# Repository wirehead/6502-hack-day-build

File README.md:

# A 6502 Computer hack

## Step 0: Acquire parts

I'd purchased from Jameco a pair of 65C02's, a pair of 65C22's, a 6551, a MAX707 equivalent, plus some Am29F010 Flash RAM and some SRAM like ten years ago and it spent the years haunting me.

I'd intended to make my own Flash RAM burner but decided that was it's own project, so I decided to borrow the design for an EEPROM burner and decided that I might as well just get one of those reasonably cheap device burners off of Amazon instead.

I also picked up some fresh breadboards because I didn't want to evict my past project from it's board just yet.

## Step 1: Reset Circuit

*Start of hack day project*

Goal: There must be a circuit that will reset the CPU when the power comes up and de-bounce the reset button.

For whatever reason when I picked up the bits, MAX707's was a cheap microprocessor supervisor device that was available.  It'll send a reset pulse, it's got an input for a button that it'll debounce, it can send a brownout warning if you configure it right, and it's got both inverted and regular RESET rails.

I used a USB breakout adapter to drive the 5v rails.

## Step 2: Clock

Goal: There must be a 1 MHz clock.

I've got a half-can TTL oscillator.  Normally I manage to install them improperly because the dots are weird, so I had to look for the edge that's not rounded off and use that as a reference.

A lot of people start off with a crystal oscillator.  The problem with that is that you then wonder "Hey, did I do the oscillator right?" and goink with a capacitor somewhere in the 20 pF range and it sucks.  I went for a oscillator because those are dead-simple by comparison.

## Step 3: CPU going straight into a NOP generator

Goal: Get the CPU free-running on a NOP instruction

There's two ways to do this.  One way is really simple but ever-so-slightly unsafe, the other way is much safer.  You can either directly wire the binary pattern for a NOP instruction using wires to +5V and GND.  Or you can put resistors there, so that it won't fry if you get the bit pattern wrong and the CPU tries to write to the data bus.

I picked the second route, which means that D1, D3, D5, D6, and D7 all have a 4.7k ohm resistor to the +5V line and the three other lines (D0, D2, D4) are all tied to 47 ohm resistor on the GND line.

http://www.6502.org/mini-projects/nop-gen/nop-gen.htm

On Amazon, I got some ribbon cable that was already crimped to cute little one-pin housings.  I've divided these into little 8 bit bus lines and I'm routing them to where the Flash RAM is eventually going to live.

## Step 4: CPU + Flash RAM

Goal: Attach a device to the databus.

Okay, a few steps at once.

The goal is to have a relatively friendly modern build environment going.  I found one project that was actually showing how to use cc65 and makefiles as your build environment.  So that got me started on having a generated HEX file that I could burn to the ROM.

The Flash ROM has a slightly longer loop going.

The memory map here is pretty much:
 - 0x0000-0x7FFF - The first 32k of the flash ROM
 - 0x8000-0xFFFF - The first 32k of the flash ROM, mirrored

## Step 5: Attempt to connect CPU + Flash RAM + ACIA + Simple address decoder and experience voltage sag

Goal: Get to the point where my desktop computer will talk to the 6502

In the days of yore, you'd wire up an RS232 port to your computer.  This meant that you needed an extra chip to do the voltage conversion, generally a MAX232.  These days, pretty much everyone standardized on the FTDI connector, which is 2 signal lines, the RX and TX lines, and power and ground, in a 6 pin header that all of the popular USB serial port breakout boards connect to.

So I get my USB serial breakout adaptor connected, the Flash RAM and the ACIA.

The memory map here is pretty much:
 - 0x0000-0x7FFF - The ACIA, repeated every 4 bytes
 - 0x8000-0xFFFF - The first 32k of the flash ROM

It didn't work.

I had a few wires not correctly inserted into the right places, so I fixed that.

But the clock wasn't getting output from the Phi-1 and Phi-2 pins, and everything was stopped.

It took me a while.  I kept suspecting that the RESET line was the wrong one because it didn't seem to be triggering.  I figured out after a while that the power LED I'd helpfully added on the board felt dim, so I pulled the voltmeter out and realized that the voltage was around 3v, and the MAX707 triggers at 4.65V.

## Step 5.1: Voltage sag fix

I tried a few things.  It seemed to get a little bit better once I added duplicate power lines, but it was still floating around 4v - 4.2v.  I checked and I'm "only" using 80 mA of power.

I tried every USB adapter I had around to see if it was a crappy adaptor.

I'm not sure if it's a crappy breadboard or just all breadboards are like that.

I could have probably soldered up a point-to-point board, except I didn't have the sockets for all of the part sizes, nor did I have a sufficently large board... and that whole process is annoying.

*So, this is where the hack-day ended.*  But Hack Day is there till the end of the weekend, really.

Eventually, I asked on the adafruit discord and madbodger suggested and it was suggested to go to board-level regulation.  So I wired up a 12v power supply, so the power switch switches 12 volts, and then put a pair of 7805 regulators, one for each board.  And that got me to the point where I had happy 5v rails.

## Step 5.2: Single-step

I wired up a single-step clock by the end of the hack-day weekend.  This means that, instead of going at 1 MHz, I can clock one bit at a time.

Running the whole CPU + Flash RAM + ACIA stack: Inconclusive.

Running the whole CPU + Flash RAM + ACIA stack with the Flash in a tight loop: Why is the address line going in a weird direction?  Also, why are some of the lines silent with my logic probe?

I check and the silent line is within the spec for that particular part against the Rockwell datasheet.  Switch the logic probe to TTL mode and it starts to behave.  But it's going into places that it's not supposed to be going!

Switching back to the configuration from Step 3, but single-stepping:  Discover that the processor is very much not single-stepping properly anymore.  Seems like somewhere along the way I managed to zap it!

It also turns out that I only picked up one 65c02, which is a really poor life choice.

Second break: Waiting for a 65c02 to appear in the mail!

## Step 5.3: A giant step back where things start to work.

I ended up getting a few things.

First, I got a cheap $10 logic analyzer that was supported by Sigrok.  Second, I got a fresh set of chips from a different manufacturer, plus more ribbon cable so that it wouldn't risk devolving too far into a rat's nest.

Third, I decided that I'd solder up a tiny little board with the power circuit, the switch, the reset button, and the CPU clock.

I did a quick test and it looked like for a bit that the single-step clock might be a problem because it was looking a lot more like it was properly looping when I hooked up the logic analyzer.

I ended up stripping the board of most of the wiring and starting over with a fresh set of parts, starting off from having just a CPU and a NOP-generator, through the part where it runs a loop in Flash RAM.  I was able to use Sigrok to decode the values on the data bus and validate that it was doing the exact right thing.

Then I spent some time mucking around with serial lines, trying to make sure I had the right connections, and from there, I was finally able to get the serial port up.

Then I was able to go back and replace parts and determine that the 65c02 I had was somehow faulty.  Not sure if it was always bad and somehow a defective part made it into the supply chain or if I'd zapped it at some point in the past.

# Step 6: CPU + Flash RAM + ACIA + RAM

**Goal**: Make sure the board won't asplode when I plug it in.

I managed to not break the board after not working with it since last August.  I did a careful check, made sure the wires weren't plugged wrong, etc.  After doing a bunch of checks, I plug it in, connect to the serial port, and it says "▒▒▒▒▒ ▒▒▒▒▒!" instead of "Hello World!"

It turns out that one of the wires between the 6551 serial controller and the 6502 had come loose.  But, because it was so close to working, even though the firmware was setting that bit of a register, it was almost working.

**Goal**: Get RAM hooked up and IO decoded

The 6502 is really nearly useless without some RAM, maybe about 256 bytes for the zero page and 256 bytes for the stack page.  Otherwise, all you've got is three registers to work with.

Most of the modern designs tend towards a relatively friendly and easy memory mapper circuit.  We started out just using an inverter on A15 to select between the ACIA and the RAM, but now we've got two devices and they are very different sizes, so the usual approach is to put an 8-input NAND gate on A14 down to A8 to get a control line for the IO.

I was kinda following [Dirk Grappendorf's tutorial](https://www.grappendorf.net/projects/6502-home-computer/) but I got myself slightly confused at the [RAM part](https://www.grappendorf.net/projects/6502-home-computer/ram.html) of things.

What it turns out worked better for me was to just wire up the complete set of IO deciders right away to mimic the [SBC-2](http://sbc.rictor.org/sch2.html) design as well as [a later section of Dirk Grappendorf's tutorial](https://www.grappendorf.net/projects/6502-home-computer/via-ports-and-timers-blinking-led.html) before trying to hook up the RAM.

The memory map here is pretty much:
 - 0x0000-0x7EFF - The RAM
 	+ 0x0000-0x00FF - Zero Page
 	+ 0x0100-0x01FF - Stack page
 	+ 0x0200-0x7EFF - Available memory
 - 0x7F00-0x7FFF - IO, where the first few bytes are the ACIA
 - 0x8000-0xFFFF - The first 32k of the flash ROM

The whole works is getting way too unreliable.

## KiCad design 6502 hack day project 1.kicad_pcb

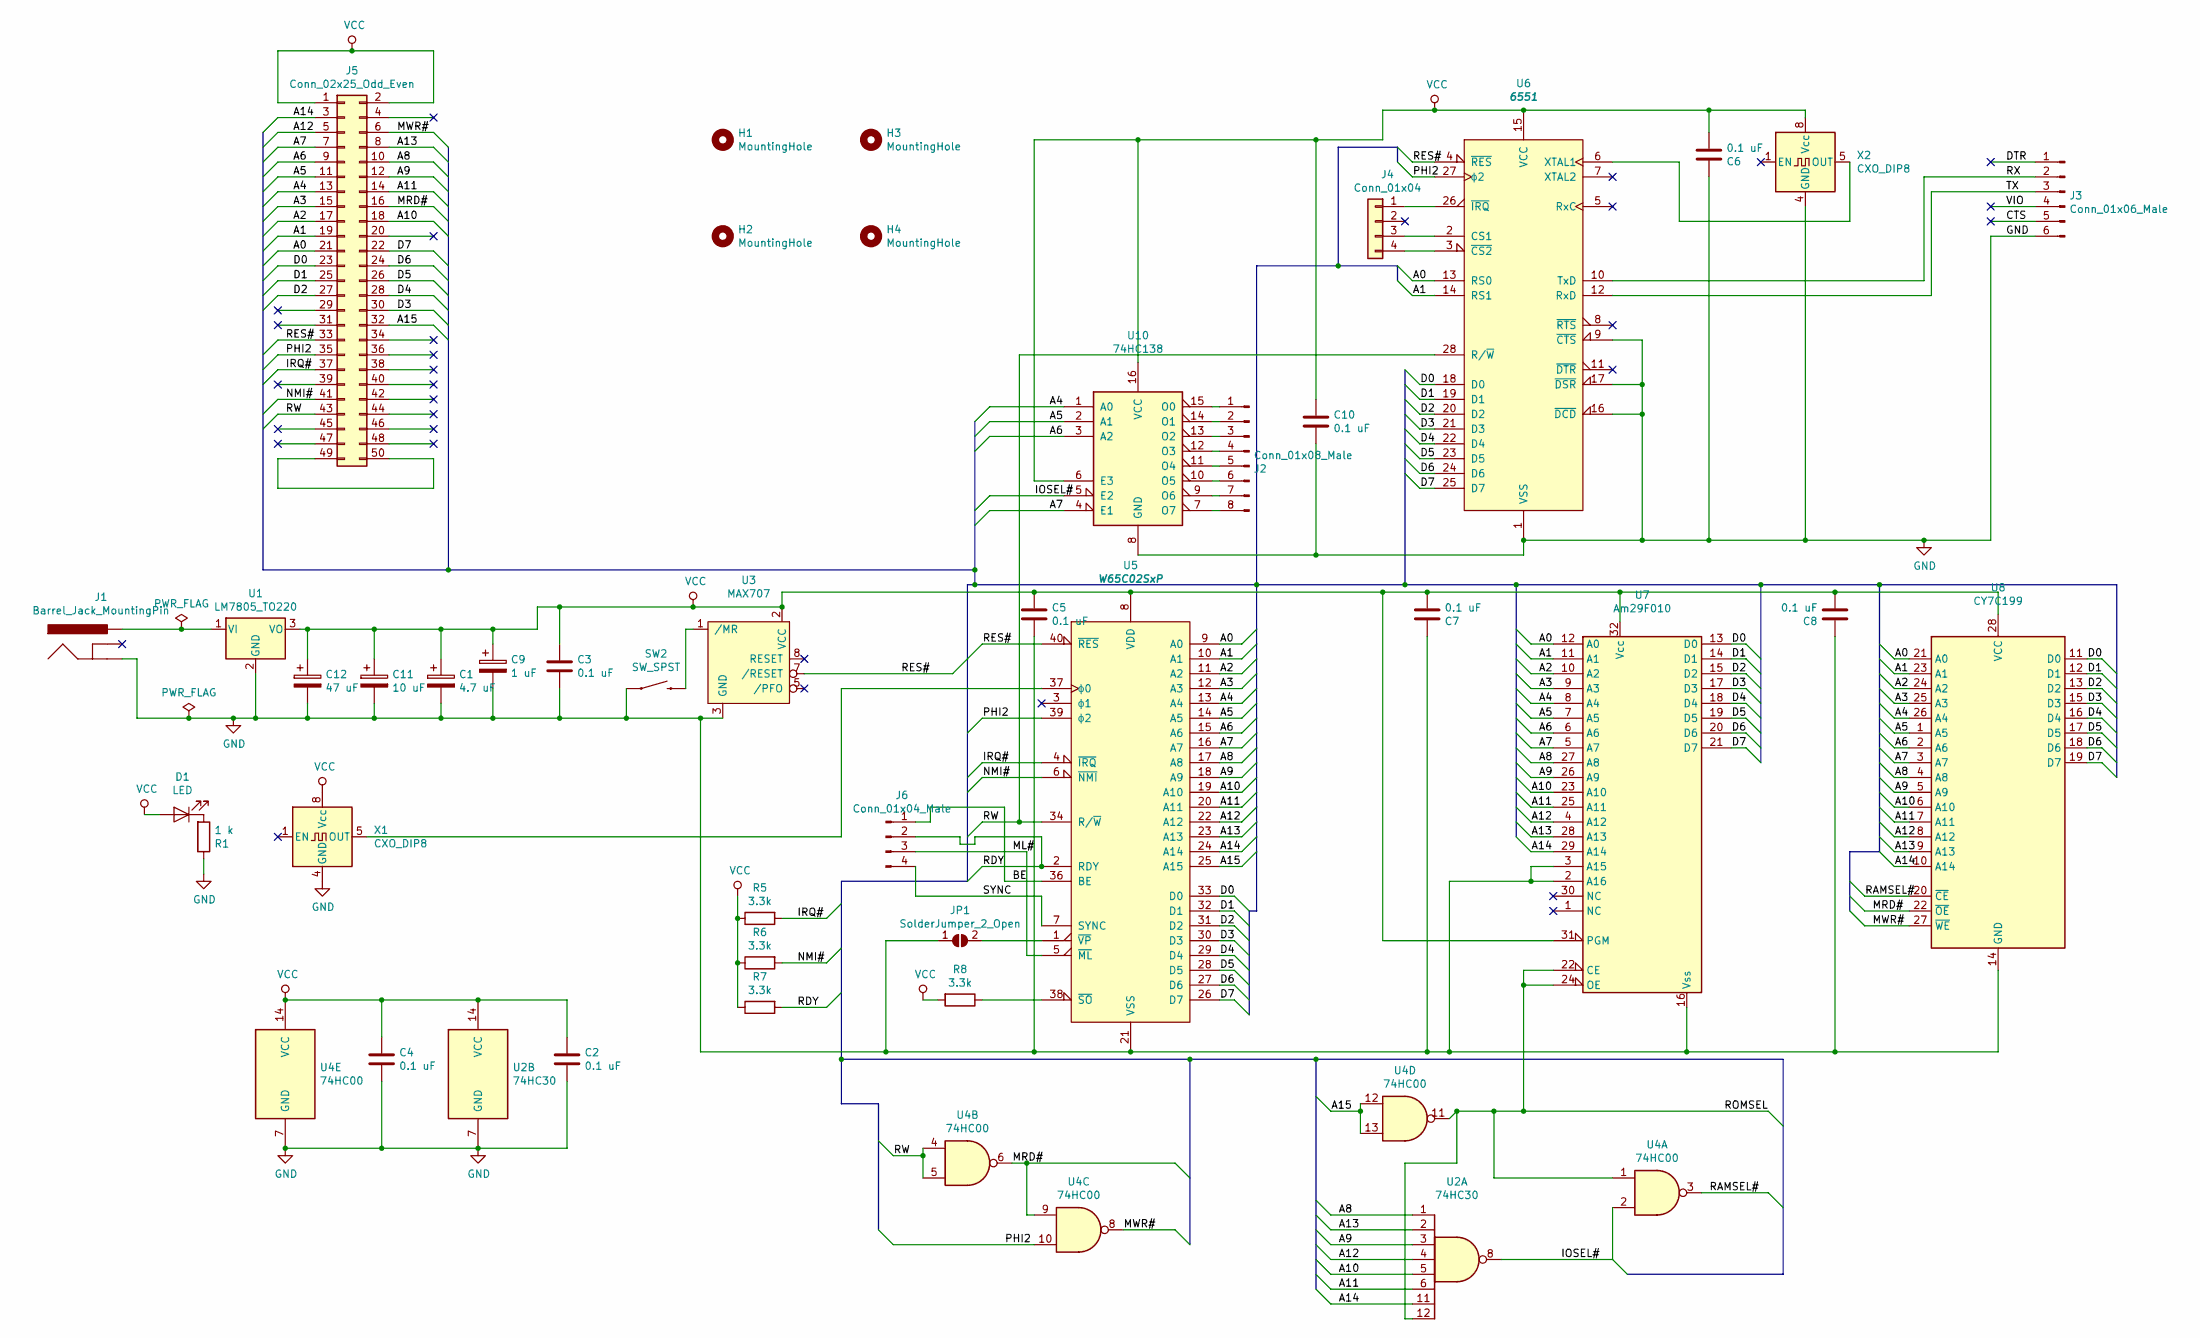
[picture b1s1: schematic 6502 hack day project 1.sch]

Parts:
C1: 4.7 uF; C_0805_2012Metric_Pad1.15x1.40mm_HandSolder
C2, C3, C4, C5, C6, C7, C8, C10: 0.1 uF; C_0805_2012Metric_Pad1.15x1.40mm_HandSolder
C9: 1 uF; C_0805_2012Metric_Pad1.15x1.40mm_HandSolder
C11: 10 uF; CP_Radial_D5.0mm_P2.00mm
C12: 47 uF; CP_Radial_D4.0mm_P2.00mm
D1: LED; LED_0805_2012Metric_Pad1.15x1.40mm_HandSolder
H1, H2, H3, H4: MountingHole; MountingHole_2.7mm_M2.5
J1: Barrel_Jack_MountingPin; POWER_JACK_PTH_BREAD
J2: Conn_01x08_Male; PinHeader_1x08_P2.54mm_Vertical
J3: Conn_01x06_Male; PinHeader_1x06_P2.54mm_Vertical
J4: Conn_01x04; PinHeader_1x04_P2.54mm_Vertical
J5: Conn_02x25_Odd_Even; PinHeader_2x25_P2.54mm_Vertical
J6: Conn_01x04_Male; PinHeader_1x04_P2.54mm_Vertical
JP1: SolderJumper_2_Open; SolderJumper-2_P1.3mm_Open_Pad1.0x1.5mm
R1: 1 k; R_0805_2012Metric_Pad1.15x1.40mm_HandSolder
R5, R6, R7, R8: 3.3k; R_0805_2012Metric_Pad1.15x1.40mm_HandSolder
SW2: SW_SPST; TACTILE_SWITCH_PTH_6.0MM
U1: LM7805_TO220; TO-220-3_Vertical
U2: 74HC30; SOIC-14_3.9x8.7mm_P1.27mm
U3: MAX707; DIP-8_W7.62mm_Socket_LongPads
U4: 74HC00; SOIC-14_3.9x8.7mm_P1.27mm
U5: W65C02SxP; DIP-40_W15.24mm_Socket_LongPads
U6: 6551; DIP-28_W15.24mm_Socket_LongPads
U7: Am29F010; DIP-32_W15.24mm_Socket_LongPads
U8: CY7C199; DIP-28_W7.62mm_Socket_LongPads
U10: 74HC138; SOIC-16_3.9x9.9mm_P1.27mm
X1, X2: CXO_DIP8; Oscillator_DIP-8

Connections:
/A0: J5.21, U5.9 (A0), U6.13 (RS0), U7.12 (A0), U8.21 (A0)
/A1: J5.19, U5.10 (A1), U6.14 (RS1), U7.11 (A1), U8.23 (A1)
/A2: J5.17, U5.11 (A2), U7.10 (A2), U8.24 (A2)
/A3: J5.15, U5.12 (A3), U7.9 (A3), U8.25 (A3)
/A4: J5.13, U5.13 (A4), U7.8 (A4), U8.26 (A4), U10.1 (A0)
/A5: J5.11, U5.14 (A5), U7.7 (A5), U8.1 (A5), U10.2 (A1)
/A6: J5.9, U5.15 (A6), U7.6 (A6), U8.2 (A6), U10.3 (A2)
/A7: J5.7, U5.16 (A7), U7.5 (A7), U8.3 (A7), U10.4 (E1)
/A8: J5.10, U2.1, U5.17 (A8), U7.27 (A8), U8.4 (A8)
/A9: J5.12, U2.3, U5.18 (A9), U7.26 (A9), U8.5 (A9)
/A10: J5.18, U2.5, U5.19 (A10), U7.23 (A10), U8.6 (A10)
/A11: J5.14, U2.6, U5.20 (A11), U7.25 (A11), U8.7 (A11)
/A12: J5.5, U2.4, U5.22 (A12), U7.4 (A12), U8.8 (A12)
/A13: J5.8, U2.2, U5.23 (A13), U7.28 (A13), U8.9 (A13)
/A14: J5.3, U2.11, U5.24 (A14), U7.29 (A14), U8.10 (A14)
/A15: J5.32, U4.12, U4.13, U5.25 (A15)
/BE: J6.1, U5.36 (BE)
/D0: J5.23, U5.33 (D0), U6.18 (D0), U7.13 (D0), U8.11 (D0)
/D1: J5.25, U5.32 (D1), U6.19 (D1), U7.14 (D1), U8.12 (D1)
/D2: J5.27, U5.31 (D2), U6.20 (D2), U7.15 (D2), U8.13 (D2)
/D3: J5.30, U5.30 (D3), U6.21 (D3), U7.17 (D3), U8.15 (D3)
/D4: J5.28, U5.29 (D4), U6.22 (D4), U7.18 (D4), U8.16 (D4)
/D5: J5.26, U5.28 (D5), U6.23 (D5), U7.19 (D5), U8.17 (D5)
/D6: J5.24, U5.27 (D6), U6.24 (D6), U7.20 (D6), U8.18 (D6)
/D7: J5.22, U5.26 (D7), U6.25 (D7), U7.21 (D7), U8.19 (D7)
/IOSEL#: U2.8, U4.2, U10.5 (E2)
/IRQ#: J5.37, R5.2, U5.4 (~IRQ)
/ML#: J6.3, U5.5 (~ML)
/MRD#: J5.16, U4.6, U4.9, U8.22 (~OE~)
/MWR#: J5.6, U4.8, U8.27 (~WE~)
/NMI#: J5.41, R6.2, U5.6 (~NMI)
/PHI2: J5.35, U4.10, U5.39 (ϕ2), U6.27 (ϕ2)
/RAMSEL#: U4.3, U8.20 (~CE~)
/RDY: J6.2, R7.2, U5.2 (RDY)
/RES#: J5.33, U3.7 (/RESET), U5.40 (~RES), U6.4 (~RES)
/ROMSEL: U2.12, U4.1, U4.11, U7.22 (CE), U7.24 (OE)
/RW: J5.43, U4.4, U4.5, U5.34 (R/~W), U6.28 (R/~W)
/RX: J3.2, U6.10 (TxD)
/SYNC: J6.4, U5.7 (SYNC)
/TX: J3.3, U6.12 (RxD)
GND: C1.2, C2.2, C3.2, C4.2, C5.2, C6.1, C7.1, C8.1, C9.2, C10.2, C11.2, C12.2, J1.GND, J3.6, JP1.1 (A), R1.1, SW2.1, U1.2 (GND), U2.7 (GND), U3.3 (GND), U4.7 (GND), U5.21 (VSS), U6.1 (VSS), U6.9 (~CTS), U6.16 (~DCD), U6.17 (~DSR), U7.2 (A16), U7.3 (A15), U7.16 (Vss), U8.14 (GND), U10.8 (GND), X1.4 (GND), X2.4 (GND)
unnamed: D1.1 (K), R1.2
unnamed: J1.PWR, U1.1 (VI)
unnamed: J2.1, U10.15 (O0)
unnamed: J2.2, U10.14 (O1)
unnamed: J2.3, U10.13 (O2)
unnamed: J2.4, U10.12 (O3)
unnamed: J2.5, U10.11 (O4)
unnamed: J2.6, U10.10 (O5)
unnamed: J2.7, U10.9 (O6)
unnamed: J2.8, U10.7 (O7)
unnamed: J4.1, U6.26 (~IRQ)
unnamed: J4.3, U6.2 (CS1)
unnamed: J4.4, U6.3 (~CS2)
unnamed: J5.49, J5.50
unnamed: JP1.2 (B), U5.1 (~VP)
unnamed: R8.1, U5.38 (~SO)
unnamed: SW2.3 (2), U3.1 (/MR)
unnamed: U5.37 (ϕ0), X1.5 (OUT)
unnamed: U6.6 (XTAL1), X2.5 (OUT)
VCC: C1.1, C2.1, C3.1, C4.1, C5.1, C6.2, C7.2, C8.2, C9.1, C10.1, C11.1, C12.1, D1.2 (A), J5.1, J5.2, R5.1, R6.1, R7.1, R8.2, U1.3 (VO), U2.14 (VCC), U3.2 (VCC), U4.14 (VCC), U5.8 (VDD), U6.15 (VCC), U7.31 (PGM), U7.32 (Vcc), U8.28 (VCC), U10.6 (E3), U10.16 (VCC), X1.8 (Vcc), X2.8 (Vcc)

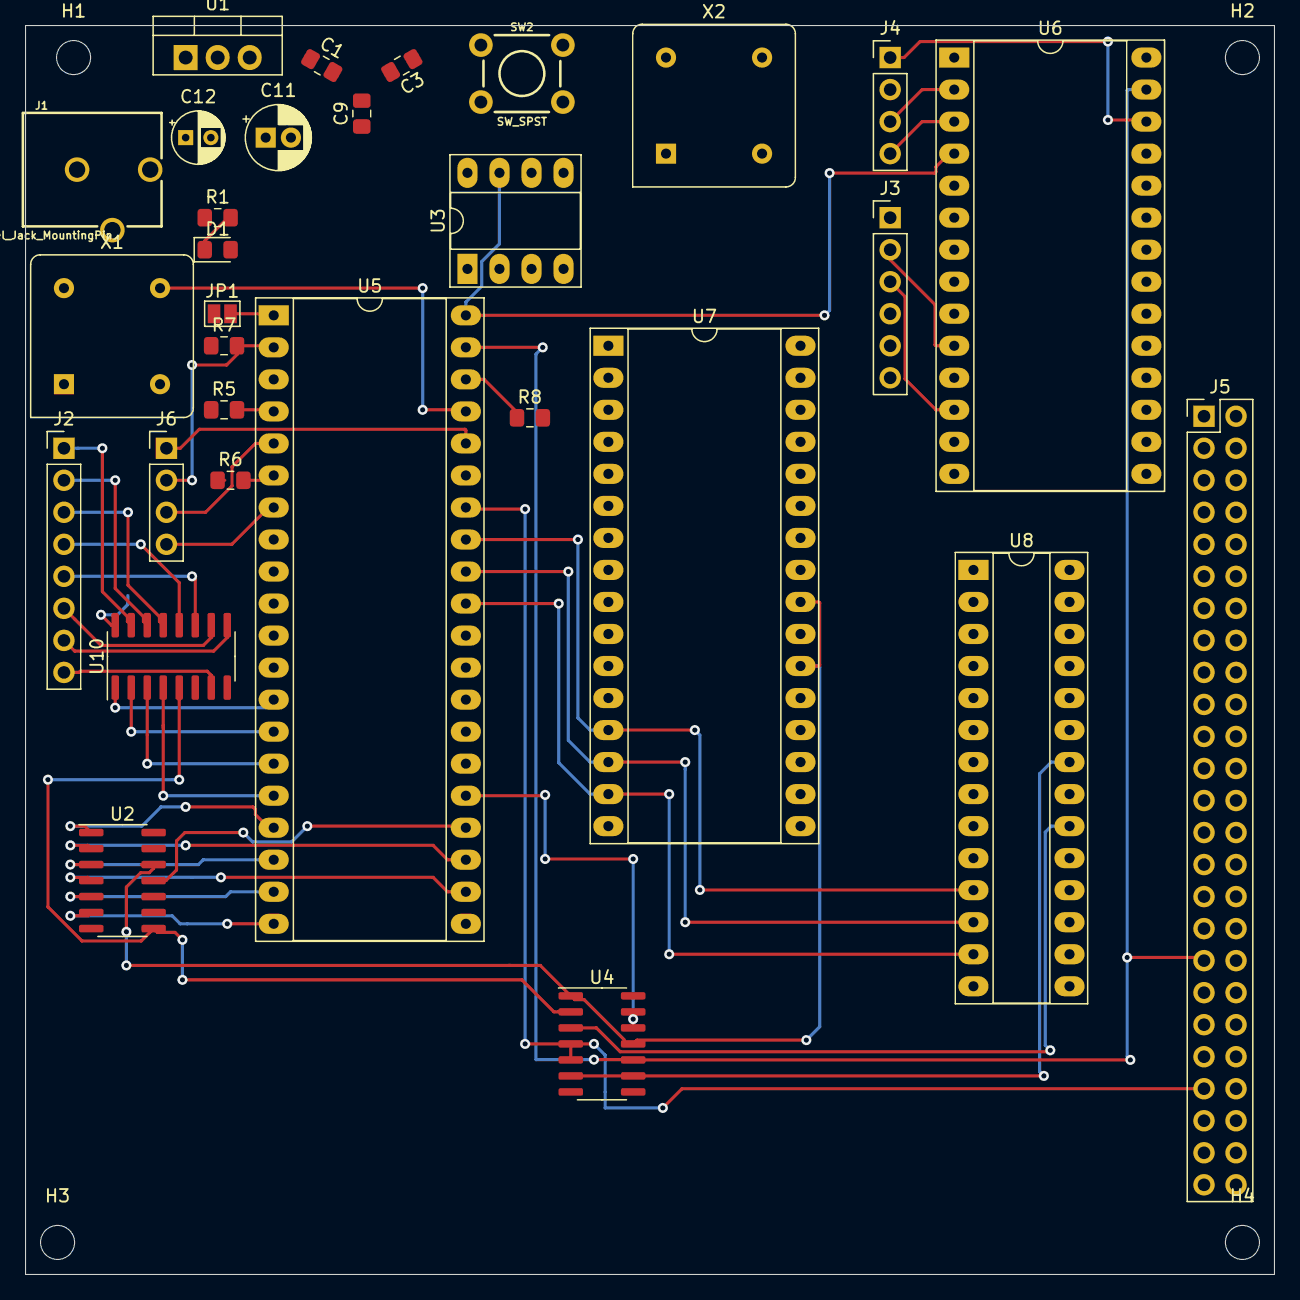
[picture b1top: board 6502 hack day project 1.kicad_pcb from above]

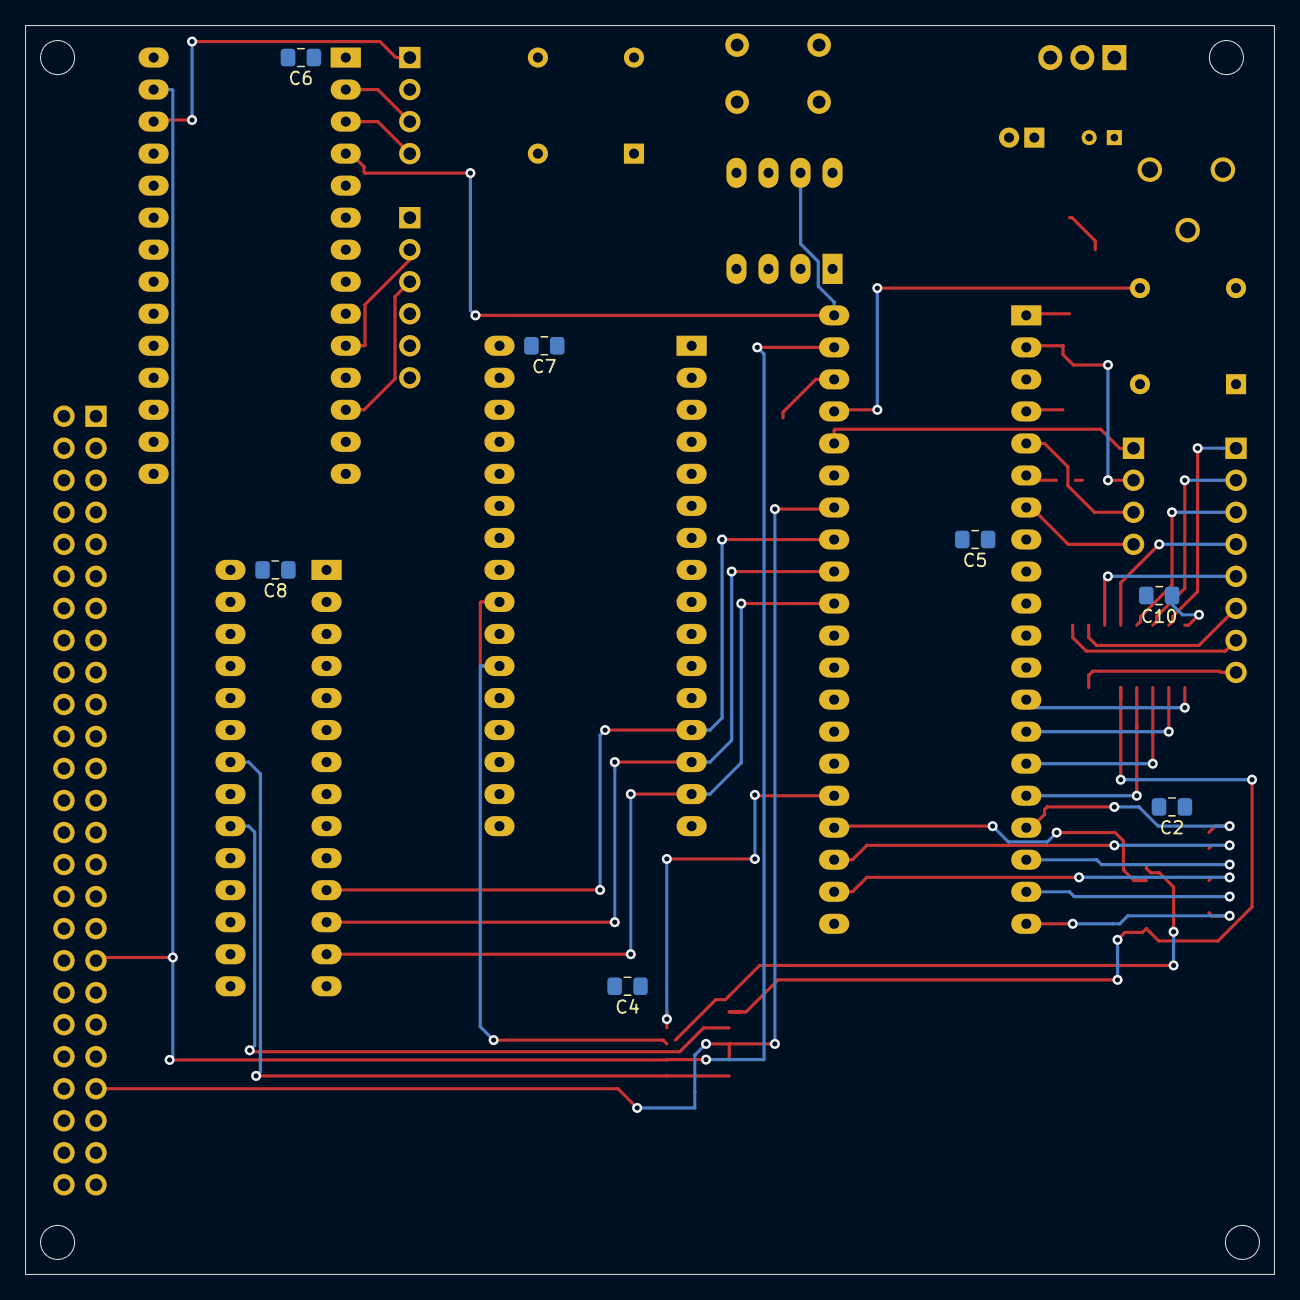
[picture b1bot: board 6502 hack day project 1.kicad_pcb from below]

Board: 2 copper layers, 99.1 x 99.1 mm, 41 parts (7 on the bottom side), 61 nets.

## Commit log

2019-06-21 starting point.
2019-06-21 clock and reset.
2019-06-21 free-run.
2019-06-21 add cache, just in cases.
2019-06-21 adding flash and flash firmware.
2019-06-24 update schematic.
2019-08-12 got the serial port working
2020-05-24 Breaking out the lines for RAM and IO.
2020-07-18 where we were at the last session
2020-07-18 Some work on turning this into a PCB
